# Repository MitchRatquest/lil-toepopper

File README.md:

# lil-toepopper
Digital audio processing unit in a guitar pedal interface with linux and puredata

To install the basics in linux, run pd_install.sh
Its helpful to have either xming and putty set up for X11 forwarding on Windows or use ssh -X

Putty's settings are Connection>SSH>X11: Enable X11, X display location localhost:0, and MIT-Magic-Cookie-1.

Still a work in progress. 

To install, run pd_install.sh, then run get_externals.sh, and finally load your pd sketch with declareALL.pd to have the libraries working correctly.

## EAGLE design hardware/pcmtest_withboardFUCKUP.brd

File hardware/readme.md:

Current hardware setup is:
OrangePi One board
16 gig microSD card
arduino nano clone
cmedia108 usb sound card

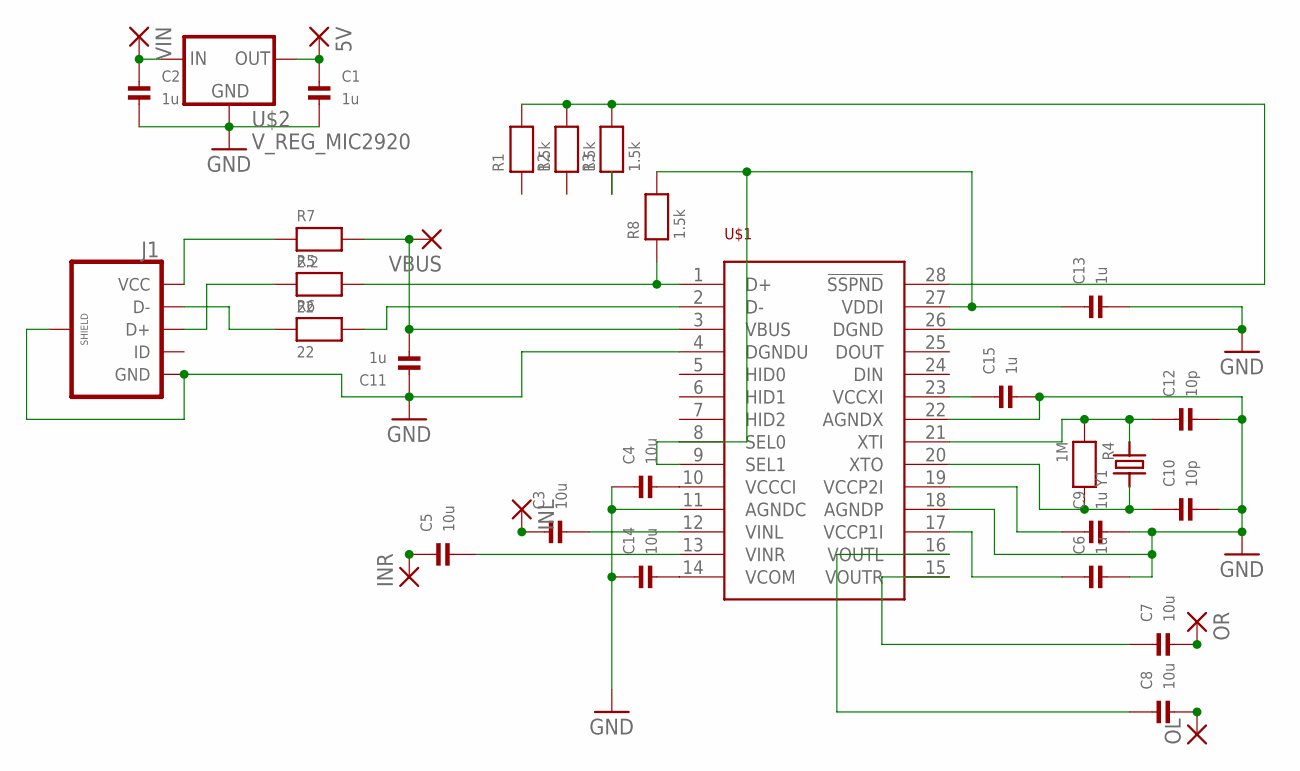
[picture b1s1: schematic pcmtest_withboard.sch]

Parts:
5V: SMD2; SMD1,27-2,54
C1, C2, C6, C9, C11, C13, C15: 1u; _0603
C3, C4, C5, C7, C8, C14: 10u; _0603
C10, C12: 10p; _0603
INL: SMD2; SMD1,27-2,54
INR: SMD2; SMD1,27-2,54
J1: USB_MICROB_PLUGCONN-11752; USB-B-MICRO-SMD_V03
OL: SMD2; SMD1,27-2,54
OR: SMD2; SMD1,27-2,54
R1, R2, R3, R8: 1.5k; _0603
R4: 1M; _0603
R5, R6: 22; _0603
R7: 2.2; _0603
U$1: PCM2906; SSOP28
U$2: V_REG_MIC2920; SOT223
VBUS: SMD2; SMD1,27-2,54
VIN: SMD2; SMD1,27-2,54
Y1: CRYSTAL2.5X2.0MM; CRYSTAL_2.5X2

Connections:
GND: C1.2, C2.2, C4.1, C6.2, C9.2, C10.2, C11.1, C12.2, C13.2, C14.1, C15.2, J1.GND, J1.SHIELD1 (SHIELD), J1.SHIELD2 (SHIELD), J1.SHIELD3 (SHIELD), U$1.4 (DGNDU), U$1.11 (AGNDC), U$1.18 (AGNDP), U$1.22 (AGNDX), U$1.26 (DGND), U$2.2 (GND)
unnamed: C3.1, INL.1
unnamed: C4.2, U$1.10 (VCCCI)
unnamed: C5.1, INR.1
unnamed: C7.2, OR.1
unnamed: R5.2, R8.1, U$1.1 (D+)
unnamed: R6.2, U$1.2 (D-)
unnamed: J1.D-, R6.1
unnamed: J1.D+, R5.1
unnamed: 5V.1, C1.1, U$2.3 (OUT)
unnamed: C2.1, U$2.1 (IN), VIN.1
unnamed: J1.VBUS (VCC), R7.1
unnamed: C11.2, R7.2, U$1.3 (VBUS), VBUS.1
unnamed: C13.1, R8.2, U$1.8 (SEL0), U$1.9 (SEL1), U$1.27 (VDDI)
unnamed: C5.2, U$1.13 (VINR)
unnamed: C3.2, U$1.12 (VINL)
unnamed: C8.2, OL.1
unnamed: C14.2, U$1.14 (VCOM)
unnamed: R1.2, R2.2, R3.2, U$1.28 (!SSPND)
unnamed: C15.1, U$1.23 (VCCXI)
unnamed: C12.1, R4.1, U$1.21 (XTI), Y1.3 (2)
unnamed: C10.1, R4.2, U$1.20 (XTO), Y1.1
unnamed: C9.1, U$1.19 (VCCP2I)
unnamed: C6.1, U$1.17 (VCCP1I)
unnamed: C8.1, U$1.16 (VOUTL)
unnamed: C7.1, U$1.15 (VOUTR)

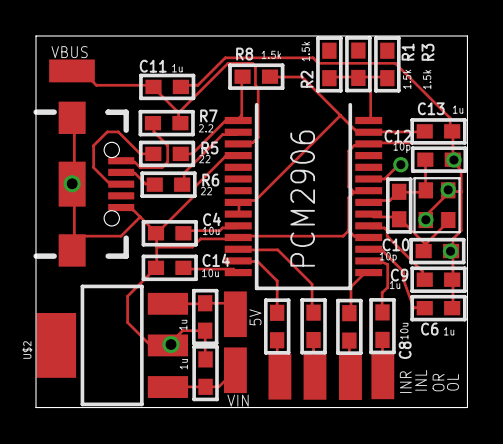
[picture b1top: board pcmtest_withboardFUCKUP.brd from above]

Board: 2 copper layers, 24.0 x 20.6 mm, 34 parts (1 on the bottom side), 26 nets.

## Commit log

2016-04-06 Create todo
2016-04-06 Update todo
2016-04-07 orangepi one board schematics
2016-04-07 arduino nano input controller
2016-04-07 quick jpg screenshot of eaglecad
2016-04-07 arduino OSC and serial display
    Really quick hack to combine the 4 character display serial input (plus commands) with OSC sending the input events at 57600 baud
2016-04-07 demo of ip to screen
2016-04-07 added gif for eye candy
2016-05-16 missing pd files
    startup opens pd with correct settings, UnpackOSC handles OSC IO and serial screen display, freeverb is a quick and dirty sketch using the plugin freeverb
2016-06-12 puredata from source script
    Direly needed this script in one place instead of all over the internet. Tested working on Armbian 5.14 with an Orange Pi PC
2016-06-12 pd_install had some weird encoding
    this works now
2016-06-12 added alsactl restore
    and exporting display didn't work, have to manually
    export DISPLAY=localhost:10.0
2016-06-13 quick-get externals
    dirty hack using my own ftp server
    gonna upload compiled externals to github proper later
2016-06-13 how to import an external in puredata
    pd-vanilla doesn't have the [import] function as in pd-extended, so here are 2 examples for doing it in-patch on load
2016-06-13 figured out move command
    untested
2016-06-13 zipped externals on FTP
    old transfer time: 17 minutes
    new transfer time: about 10 seconds
2016-06-13 declare all externals on pd startup
    include this lil guy in your pd startup options and every library in externals will be loaded
2016-06-13 note to future self
    combine this so it is system agnostic wrt naming conventions and /home/$USER/externals with USER="$( logname )"
2016-06-13 externals
2016-06-13 quick integration
    added declareALL.pd generator so you don't have to manually do it, puts it in ~/declareALL.pd for easy calling on your pd startup
2016-06-13 alsactl quirk
2016-06-13 externals zip
    had to remove the GEM library as its not tested, doesn't have good support on allwinner chips, and I really don't need it at the moment.
    If you want it, feel free to request it. The zip file was slightly too large to upload to github with GEM.
2016-06-13 changed exec permissions on scripts
2016-06-19 added version control?
    untested
2016-06-19 corrected versioning mistakes
    Should be able to automatically install correct source based on processor type
2016-06-19 improved gzip to tar
    found a pipe command which works just as well
2016-06-20 i686 addition
2016-06-20 catchall for source grabbing
2016-08-23 remove jack
    stalls the install for user input
    added -j 4 make option
2016-12-15 PCM2906 soundcard files
2016-12-15 Rename pcmtest_withboardFUCKUP.brd to pcmtest_withboard.brd
2016-12-15 Rename pcmtest_withboardFUCKUP.sch to pcmtest_withboard.sch

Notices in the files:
parts and their libraries:
SparkFun-Connectors: Licensing: Creative Commons ShareAlike 4.0 International - https://creativecommons.org/licenses/by-sa/4.0
microbuilder: This work is placed in the public domain, and may be freely used for commercial and non-commercial work with the following conditions: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
